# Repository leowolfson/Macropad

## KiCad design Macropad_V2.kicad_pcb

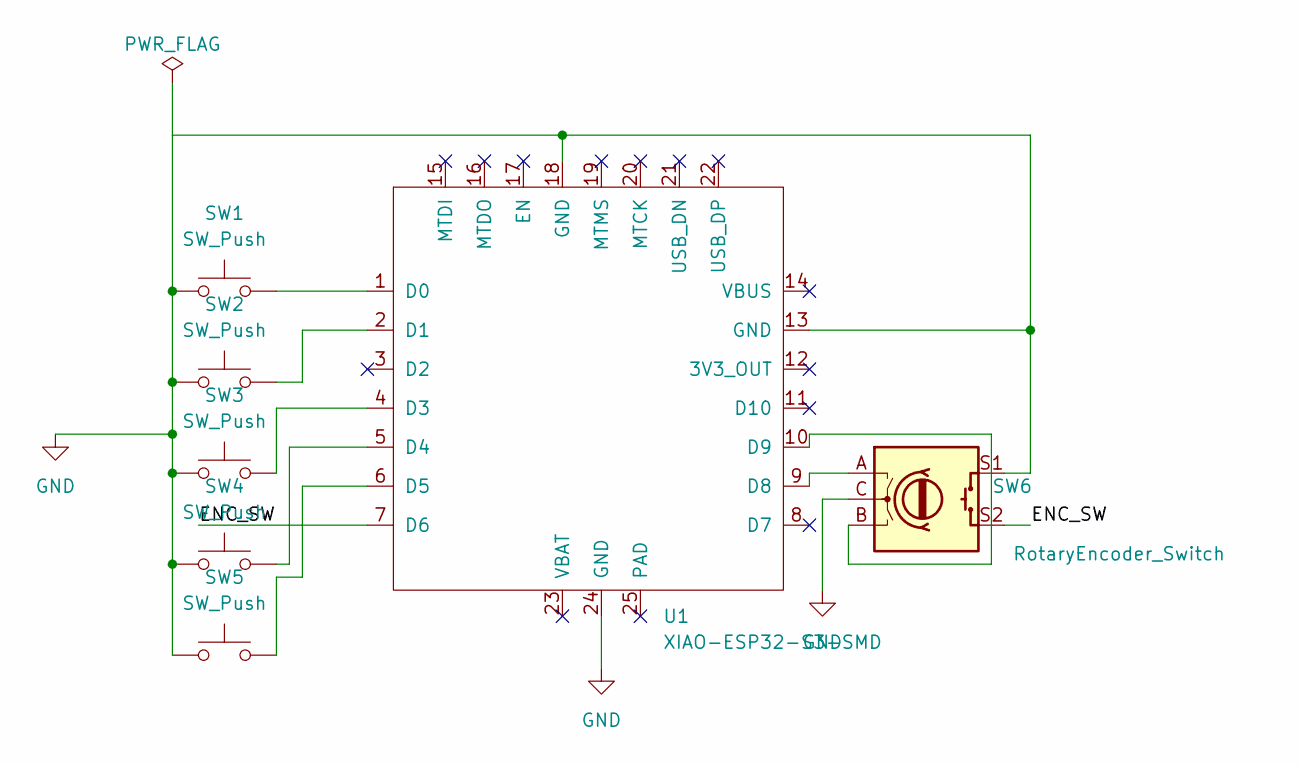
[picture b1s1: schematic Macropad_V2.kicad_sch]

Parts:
SW1, SW2, SW3, SW4, SW5: SW_Push; SW_Cherry_MX_1.00u_PCB
SW6: RotaryEncoder_Switch; RotaryEncoder_Alps_EC11E-Switch_Vertical_H20mm
U1: XIAO-ESP32-S3-SMD

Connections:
/ENC_SW: SW6.S2, U1.7 (D6)
GND: SW1.1, SW2.1, SW3.1, SW4.1, SW5.1, SW6.C, SW6.S1, U1.13 (GND), U1.18 (GND), U1.24 (GND)
unnamed: SW1.2, U1.1 (D0)
unnamed: SW2.2, U1.2 (D1)
unnamed: SW3.2, U1.4 (D3)
unnamed: SW4.2, U1.5 (D4)
unnamed: SW5.2, U1.6 (D5)
unnamed: SW6.A, U1.9 (D8)
unnamed: SW6.B, U1.10 (D9)

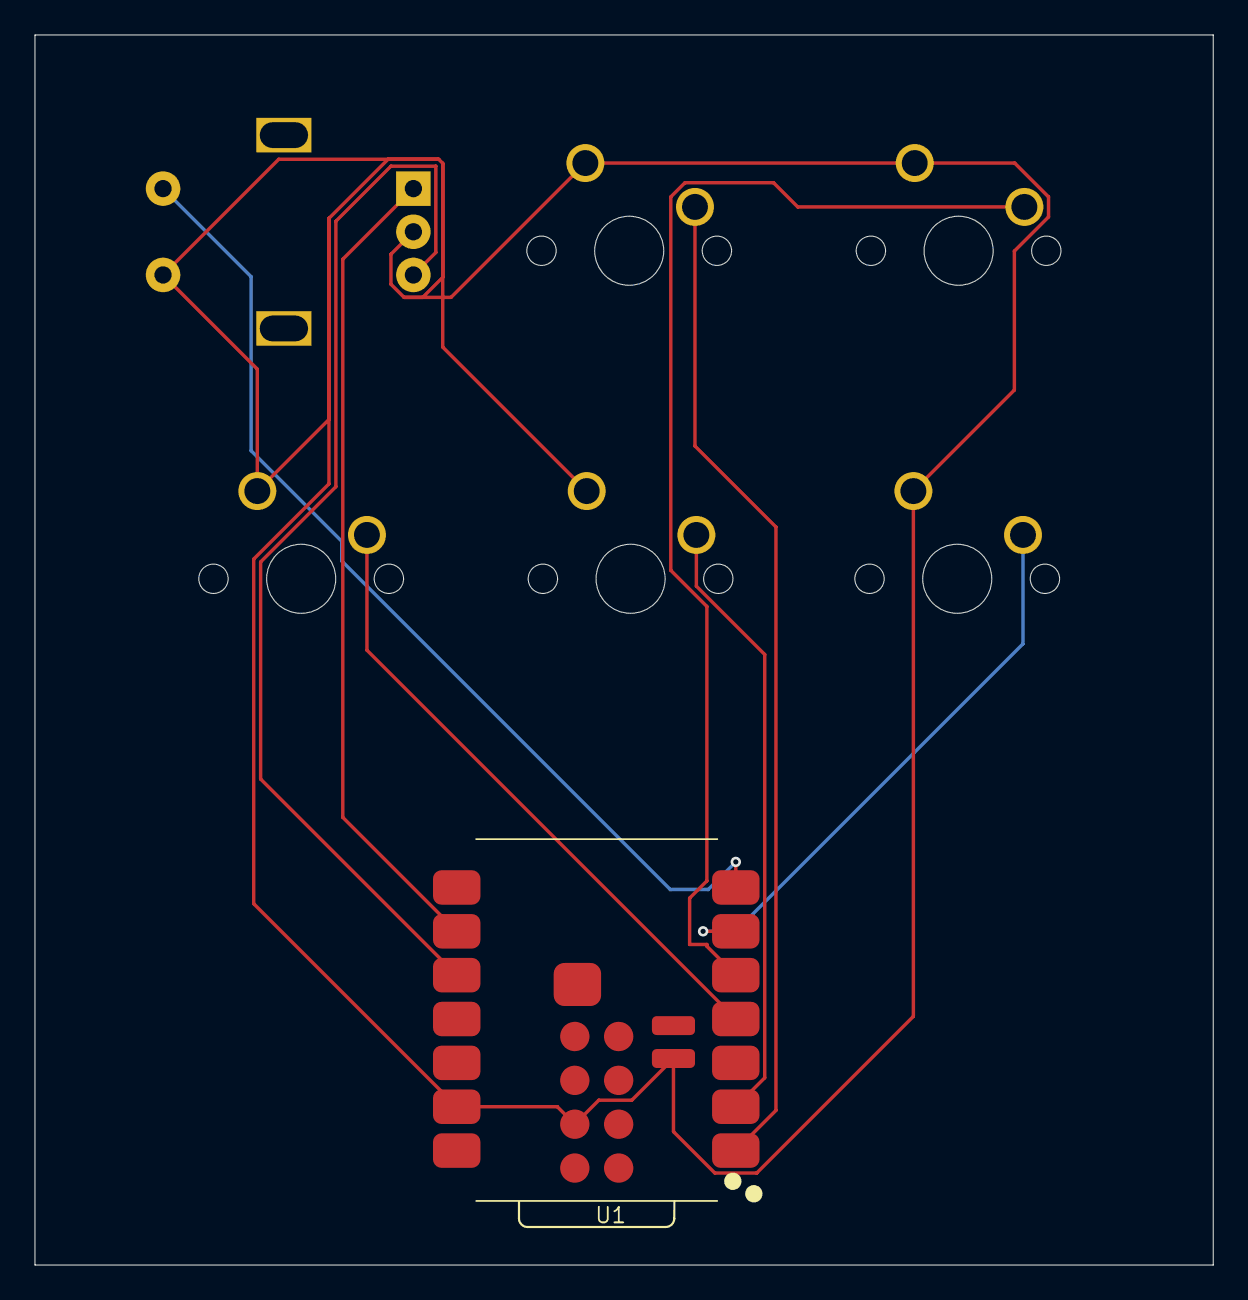
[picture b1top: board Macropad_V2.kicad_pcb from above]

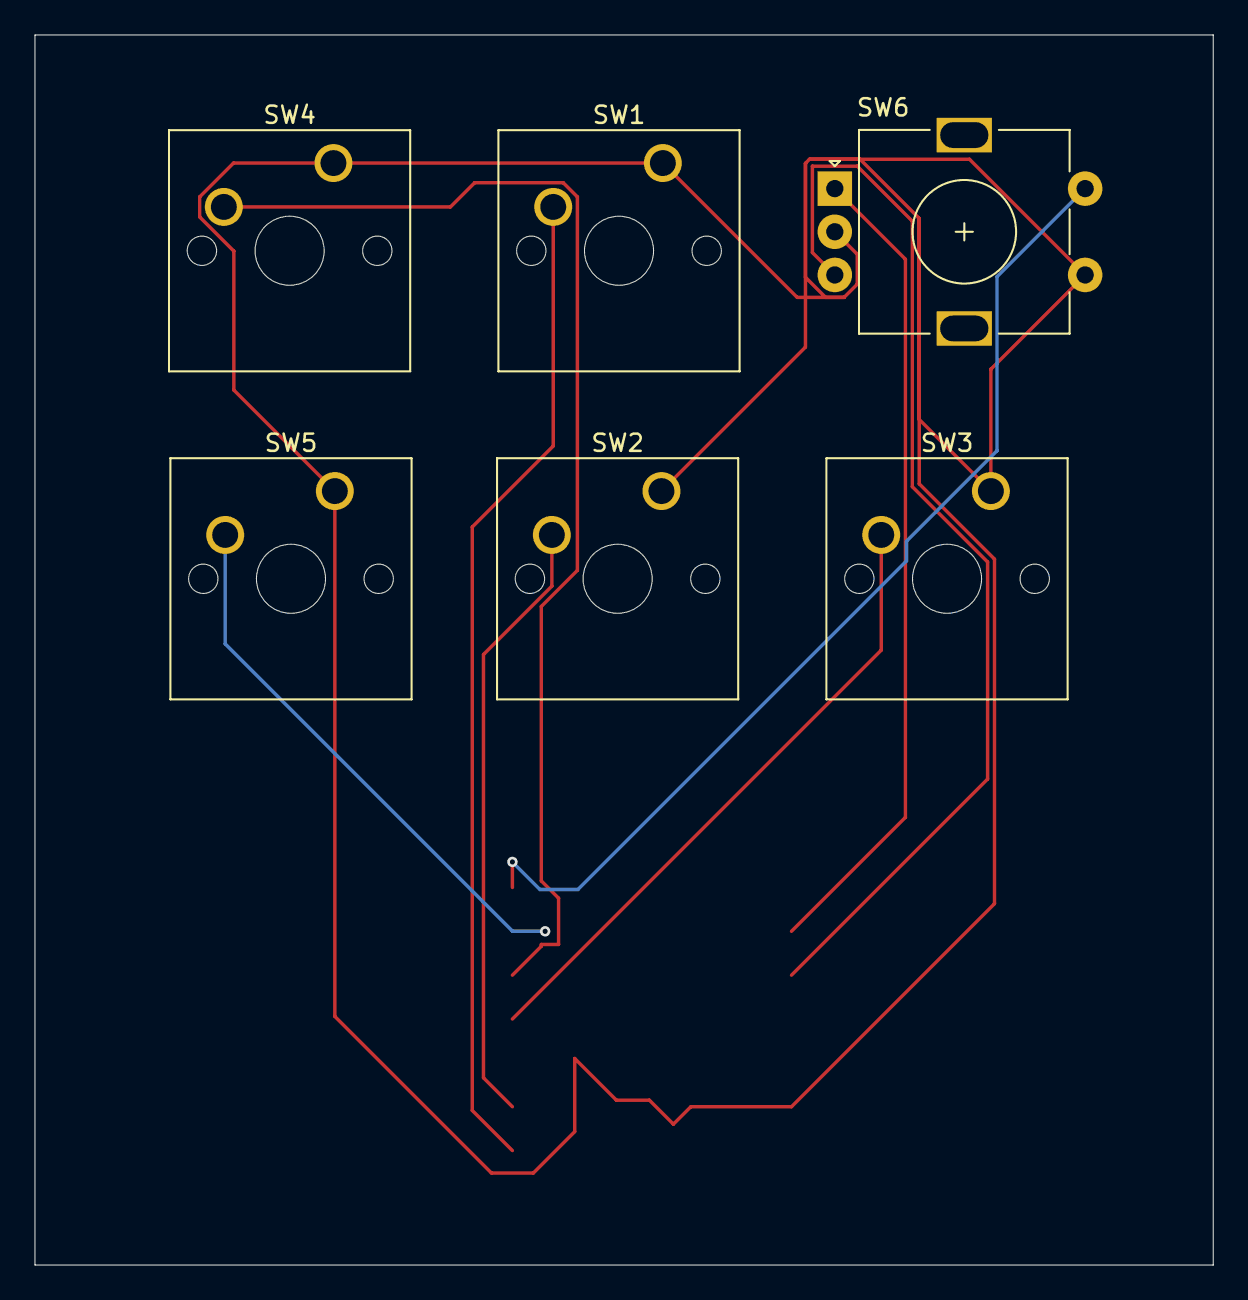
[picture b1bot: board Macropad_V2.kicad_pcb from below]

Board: 2 copper layers, 68.2 x 71.2 mm, 7 parts (6 on the bottom side), 9 nets.
